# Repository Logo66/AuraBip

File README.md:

# AuraBip — BLE-Vario auf Heltec V4 (Arbeitstitel)

Minimalistisches BLE-Vario im Stodeus-Stil: Heltec WiFi LoRa 32 V4 + GNSS +
BMP581 + LSM6DSO32 + SHT40. OLED zeigt nur das Nötigste, maximal gross.
Zwei Varianten: **silent** (BLE+Display) und **audio** (I2S-Verstärker,
Vario-Ton + Sprachansagen).

© 2026 KIE Engineering. Proprietär. Clean-Room-Regel wie WindBuddy:
kein Code aus GPL/CC-BY-NC-Projekten (GXAirCom, SoftRF, etc.).
Erlaubt: RadioLib/NimBLE/U8g2 als Bibliotheken (MIT/BSD), öffentliche
Protokoll-Spezifikationen (LK8EX1, NMEA).

## Kernidee "Instant Vario"

Reines Baro-Vario ist träge und böenempfindlich. Die Franzosen (Stodeus)
koppeln deshalb Beschleunigungssensor + Barometer. Wir machen dasselbe:
Kalman-Filter mit BMP581 (Messung, ~50 Hz) + LSM6DSO32 Vertikal-
beschleunigung (Prädiktion, ~200 Hz). Ergebnis: Ansprechzeit <100 ms statt
~1 s, ohne Zappeln.

## BLE-Protokoll (Kompatibilität zu XCTrack / XCSoar / SkyDrop-Apps)

Nordic UART Service (NUS), Notify-Stream mit:
- `$LK8EX1,<press_Pa>,<alt_m>,<vario_cm_s>,<temp_C>,<batt>*CS` — 5 Hz
- NMEA `$GPGGA` / `$GPRMC` Passthrough vom GNSS — 1 Hz
⚠️ VERIFY: LK8EX1-Feldreihenfolge/Checksumme gegen offizielle Doku (T1).

## Display-Philosophie

128×64 OLED, eine einzige Ansicht im Flug:
```
+----------------------+
|  +2.4          ← Vario, riesig (32 px Ziffern)
|  1847 m   34 km/h    ← Alt + GPS-Speed, klein
+----------------------+
```
Kein Menü im Flug. Konfiguration über BLE (BipLink-Prinzip) — Ticket T5.

## Audio-Variante — Realitätscheck

"High Quality Sprach- und Varioton" geht NICHT über den nackten Piezo.
Stodeus-Qualität heisst: richtiger Lautsprecher + Verstärker.
Unser Weg: **MAX98357A I2S-Amp (~3 CHF) + 1 W / 8 Ω Lautsprecher 20–28 mm**.
- Varioton: Synthese direkt auf dem S3 (Sinus/Rechteck, Tonhöhe+Rate aus Vz)
- Sprache: WAV-Samples (16 kHz mono) im 16-MB-Flash — Ansagen Höhe/Speed/
  Steigen auf Doppeltipp (IMU-Tap-Detection des LSM6DSO32, kein Taster nötig!)
Samples: selbst mit TTS generieren (de/en/es — es für Kolumbien 😉).

## Hardware-Verkabelung (v0.1 Prototyp)

| Signal | Heltec V4 Pin | Anmerkung |
|---|---|---|
| I2C SDA/SCL | 17 / 18 (⚠️ VERIFY am V4-Schema) | BMP581 0x47, LSM6DSO32 0x6A, SHT40 0x44 — Ivos Standard-Map |
| GNSS | SH1.25-8P Connector | ⚠️ VERIFY Pinout/UART lt. V4-Doku (T2) |
| OLED | onboard | SSD1306 128×64 |
| I2S (audio) | BCLK/LRCK/DIN frei wählen | in config.h |

## Strategie-Notiz

Hardware-Kosten ~35–45 CHF (Board+Sensoren+GNSS). Als Bausatz das perfekte
Einstiegsprodukt unterhalb der Aura Krücke — und der SX1262 ist ja onboard:
FANET-Upgrade per Firmware-Update ist der eingebaute Upsell (v2).

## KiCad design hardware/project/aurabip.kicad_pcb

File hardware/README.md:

# AuraBip audio — Hardware v0.1 (Serienprodukt)

© 2026 KIE Engineering. Proprietär.

Kompaktes BLE-Vario mit Ton-/Sprachausgabe **und FANET-TX** (FANET→OGN;
ADS-L-ready für den kommenden Conspicuity-Standard): **36×52 mm, 4 Lagen, doppelseitig bestückt**.
Vorderseite: MCU, Sensorik, GNSS, Audio, Power. Rückseite: E22-900M22S
(SX1262) + u.FL-Antennenbuchse. OLED-Modul gesteckt über der Vorderseite,
Akku (LiPo 802030) und Lautsprecher extern per JST-PH.

## Struktur

```
hardware/
  BOM.md          Stückliste + bewusste Design-Entscheide + VERIFY-Tickets
  PINMAP.md       GPIO-Zuordnung, Power-Topologie, komplette Netzliste
  lib/            aurabip.kicad_sym + aurabip.pretty (eigene Symbole/Footprints)
  project/        aurabip.kicad_sch / aurabip.kicad_pcb (generiert!)
  scripts/        generate_schematic.py / generate_pcb.py / symlib.py
  route/          FreeRouting-Pipeline (fanout -> DSN -> route -> import -> DRC)
```

**Alles generiert:** Schema und PCB entstehen aus den Python-Skripten —
Änderungen bitte dort machen und neu generieren, nicht im GUI editieren
(sonst divergiert die Quelle der Wahrheit). Workflow:

```powershell
# 1. Schema (schreibt auch lib/aurabip.kicad_sym + Lib-Tables)
& "C:\Program Files\KiCad\10.0\bin\python.exe" scripts\generate_schematic.py
# 2. ERC
& "C:\Program Files\KiCad\10.0\bin\kicad-cli.exe" sch erc project\aurabip.kicad_sch
# 3. PCB (Platzierung + Zonen, ohne Tracks; zieht Netzliste aus dem Schema)
& "C:\Program Files\KiCad\10.0\bin\python.exe" scripts\generate_pcb.py
# 4. Routing + DRC
powershell -File route\run_autoroute.ps1   # -> project\aurabip_routed.kicad_pcb
```

## Floorplan (Blick von oben)

```
+--------------------------------+
|      L96 GNSS (Patch oben)     |  <- Antenne Richtung Himmel
|                        [AKKU]  |
| ESP32-S3    BMP581  SHT40      |
| (Antenne    LSM6DSO32   [OLED- |
|  -> links)  Pullups      Hdr]  |
| LDO  Teiler  MAX98357A         |
| SW1  USBLC6  Lader  [SPEAKER]  |
| [RST] USB-C [BOOT]  Testpads   |
+--------------------------------+
```

- **ESP32-Antenne**: linke Kante, Kupfer-Keepout auf allen Lagen (x 0–6.0, y 17.7–34.3)
- **L96-Patch**: obere Kante, GND-Lage bleibt darunter (Quectel-Empfehlung, VERIFY T-H5)
- **BMP581/SHT40**: nahe Boardkante; fürs Gehäuse Druckausgleichs-/Lüftungsöffnung vorsehen
- **Rückseite**: E22-900M22S mittig (Handbestückung), u.FL darunter — 868-Flexantenne
  im Gehäuse verlegen, weg von GNSS-Patch und BLE-Antenne (T-H8)
- Lagen: F=Signal+GND-Pour, In1=GND, In2=+3V3, B=Signal+GND-Pour

## Fertigung

- JLCPCB 4-Lagen, 1.6 mm, min. Track/Clearance 0.10 mm (Via 0.5/0.3),
  Bohrloch→Kupfer 0.2 mm — Standardprozess (T-H1 verifizieren)
- SMT-Bestückung (Vorderseite): alle Passiven 0402/0603 aus JLC-Basic-Sortiment
- Handbestückung: L96, JST-Stecker, OLED-Header, Rückseite (E22, u.FL, C14/C15)

## Firmware-Anpassung

Serien-Board ≠ Heltec-Prototyp — `src/config.h` braucht die Pin-Werte aus
[PINMAP.md](PINMAP.md) (I2C 8/9, GNSS 17/18, I2S 4/5/6, neu: AMP_SD 7,
VBAT_ADC 1, LED 2, BTN 0, LoRa-SPI 21/12/11/13 + BUSY 14/DIO1 3/RST 15/
TXEN 16/RXEN 37; OLED auf dem Sensorbus, kein Vext).

**FANET-TX**: Encoder aus WindBuddy `lib/fanet` übernehmen (eigener
Clean-Room-Code, Tracking Typ 1 statt Wetter Typ 4). RadioLib mit
`setRfSwitchPins(RXEN, TXEN)`. TX-Leistung hart ≤ 14 dBm ERP (T-H8),
nur im Flug senden, Adresse/Manufacturer wie WindBuddy-Konvention.

## Offene VERIFY-Tickets (vor Bestellung!)

| Ticket | Was |
|---|---|
| T-H1 | LCSC-Nummern + Lagerbestand aller Positionen |
| T-H2 | **L96-Padout** gegen Quectel Hardware Design Guide (Footprint ist Annahme!) |
| T-H3 | MAX98357A: TQFN-Pinnummern + Exposed-Pad-Maß gegen Maxim-Datenblatt |
| T-H4 | LSM6DSO32-Pinout (INT1=Pin 4?) gegen ST-Datenblatt |
| T-H5 | Antennen-Regeln: ESP32-Keepout-Maße + GND unter L96-Patch |
| T-H6 | USB-C-Footprint-Orientierung: Stecker muss über die Boardkante ragen |

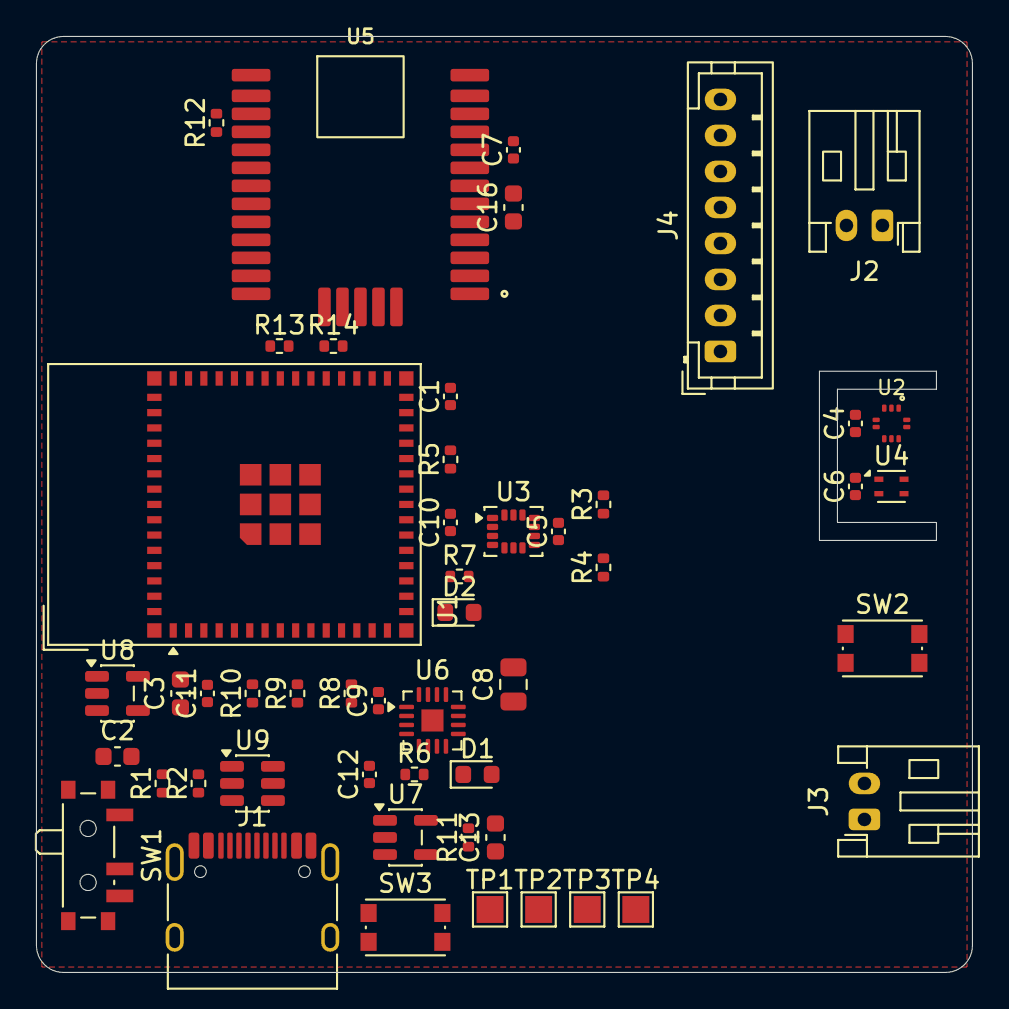
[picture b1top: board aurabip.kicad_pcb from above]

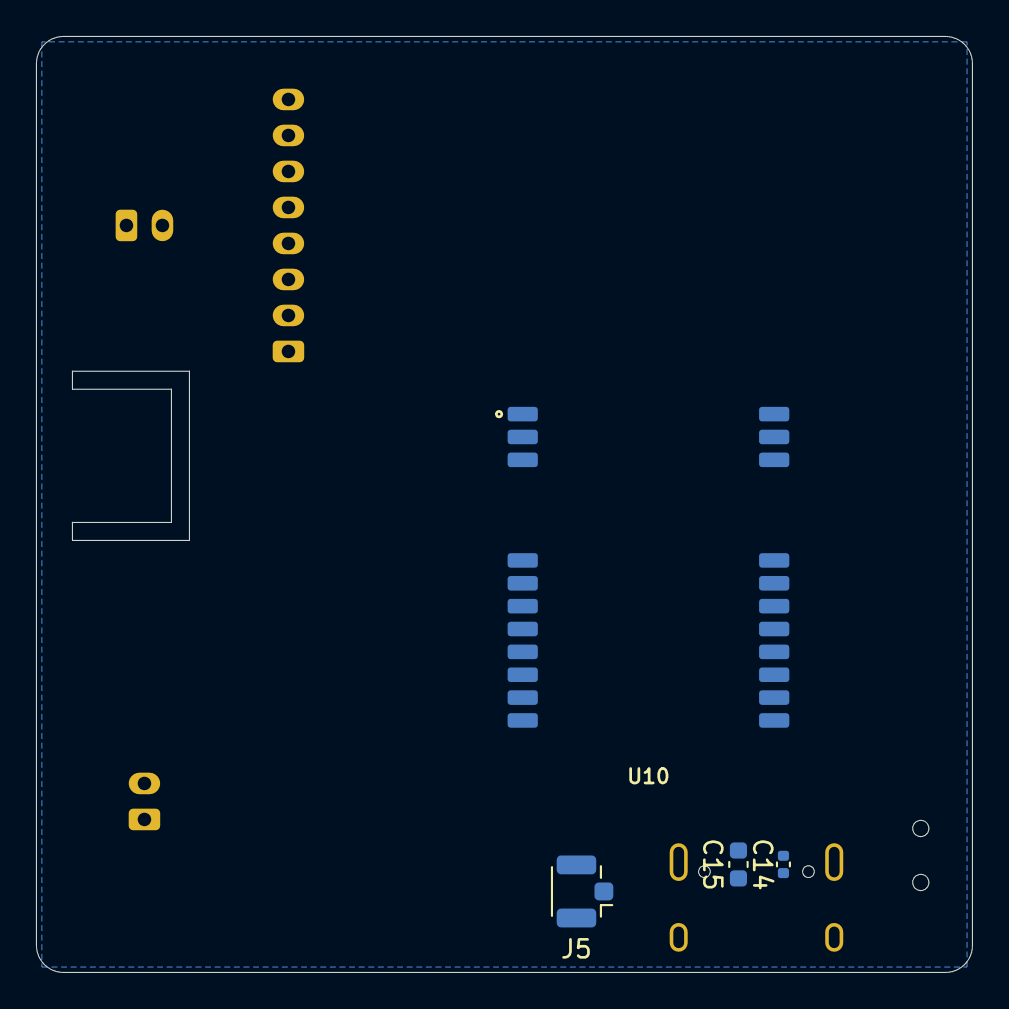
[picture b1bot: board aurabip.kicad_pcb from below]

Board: 4 copper layers, 52.0 x 52.0 mm, 54 parts (4 on the bottom side), 48 nets, no tracks yet.

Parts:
C1, C4, C5, C6, C7, C9, C11, C12, C14: 100n; C_0402_1005Metric
C2, C3, C15, C16: 10u; C_0603_1608Metric
C8: 22u; C_0805_2012Metric
C10: 1u; C_0402_1005Metric
C13: 4.7u; C_0603_1608Metric
D1: CHG; LED_0603_1608Metric
D2: STATUS; LED_0603_1608Metric
J1: USB-C; USB_C_Receptacle_HRO_TYPE-C-31-M-12
J2: AKKU; JST_PH_S2B-PH-K_1x02_P2.00mm_Horizontal
J3: SPEAKER; JST_PH_S2B-PH-K_1x02_P2.00mm_Horizontal
J4: OLED SPI; JST_PH_B8B-PH-K_1x08_P2.00mm_Vertical
J5: u.FL 868; U.FL_Hirose_U.FL-R-SMT-1_Vertical
R1, R2: 5.1k; R_0402_1005Metric
R3, R4: 4.7k; R_0402_1005Metric
R5: 10k; R_0402_1005Metric
R6, R7, R13: 1k; R_0402_1005Metric
R8: 100k; R_0402_1005Metric
R9, R10: 1M; R_0402_1005Metric
R11, R14: 2k; R_0402_1005Metric
R12: 0R; R_0402_1005Metric
SW1: EIN/AUS; SW_SPDT_PCM12
SW2: RESET; SW_Push_1P1T_NO_CK_KMR2
SW3: BOOT; SW_Push_1P1T_NO_CK_KMR2
TP1: IO33; TestPoint_Pad_1.5x1.5mm
TP2: IO34; TestPoint_Pad_1.5x1.5mm
TP3: IO35; TestPoint_Pad_1.5x1.5mm
TP4: IO36; TestPoint_Pad_1.5x1.5mm
U1: ESP32-S3-MINI-1; ESP32-S3-MINI-1_compact
U2: BMP581; BMP581_LGA-10_2x2mm
U3: LSM6DSO32; LGA-14_3x2.5mm_P0.5mm_LayoutBorder3x4y
U4: SHT40; Sensirion_DFN-4_1.5x1.5mm_P0.8mm_SHT4x_NoCentralPad
U5: L96; Quectel_L96
U6: MAX98357A; TQFN-16-1EP_3x3mm_P0.5mm_EP1.23x1.23mm
U7: MCP73831; SOT-23-5
U8: AP2112K-3.3; SOT-23-5
U9: USBLC6; SOT-23-6
U10: E22-900M22S; E22_900M22S

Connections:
+3V3: C1.1, C3.1, C4.1, C5.1, C6.1, C7.1, C14.1, C15.1, C16.1, J4.1, R3.1, R4.1, R5.1, R8.1, U1.3, U2.1, U2.5, U2.6, U2.10, U3.5, U3.8, U3.12, U4.3, U5.8, U5.9, U8.5, U10.9
AMP_SD: R8.2, U1.11, U6.4
BTN_BOOT: SW3.1, U1.4
CC1: J1.A5, R1.1
CC2: J1.B5, R2.1
CHG_LED_A: D1.2, R6.2
CHG_STAT: D1.1, U7.1
ESP_EN: C10.1, R5.2, SW2.1, U1.45
GND: C1.2, C2.2, C3.2, C4.2, C5.2, C6.2, C7.2, C8.2, C9.2, C10.2, C11.2, C12.2, C13.2, C14.2, C15.2, C16.2, D2.1, J1.A1, J1.A12, J1.B1, J1.B12, J1.SH, J2.2, J4.2, J5.2, R1.2, R2.2, R10.2, R11.2, R14.2, SW1.3, SW2.2, SW3.2, U1.1, U1.2, U1.42, U1.43, U1.46, U1.47, U1.48, U1.49, U1.50, U1.51, U1.52, U1.53, U1.54, U1.55, U1.56, U1.57, U1.58, U1.59, U1.60, U1.61, U1.62, U1.63, U1.64, U1.65, U2.3, U2.8, U2.9, U3.1, U3.6, U3.7, U4.4, U5.4, U5.5, U5.10, U5.11, U5.12, U5.13, U5.14, U5.15, U5.18, U5.19, U5.21, U5.22, U5.27, U5.31, U6.3, U6.11, U6.15, U6.17, U7.2, U8.2, U9.2, U10.1, U10.2, U10.3, U10.4, U10.5, U10.10, U10.11, U10.12, U10.20, U10.22
GNSS_RXD: R13.1, U1.22
GNSS_RXD_DIV: R13.2, R14.1, U5.26
GNSS_TXD: U1.21, U5.25
I2C_SCL: R4.2, U1.13, U2.2, U3.13, U4.2
I2C_SDA: R3.2, U1.12, U2.4, U3.14, U4.1
I2S_BCLK: U1.8, U6.16
I2S_DOUT: U1.10, U6.1
I2S_LRCK: U1.9, U6.14
IMU_INT1: U1.14, U3.4
L96_RFIN: R12.2, U5.17
L96_RFOUT: R12.1, U5.16
LDO_EN: SW1.2, U8.3
LED2_A: D2.2, R7.2
LED_STATUS: R7.1, U1.6
LORA_ANT: J5.1, U10.21
LORA_BUSY: U1.18, U10.14
LORA_DIO1: U1.7, U10.13
LORA_NSS: U1.25, U10.19
LORA_RST: U1.19, U10.15
LORA_RXEN: U1.33, U10.6
LORA_TXEN: U1.20, U10.7
OLED_CS: J4.5, U1.28
OLED_DC: J4.6, U1.29
OLED_RST: J4.7, U1.31
PROG: R11.1, U7.5
SPI2_MISO: U1.17, U10.16
SPI2_MOSI: J4.3, U1.15, U10.17
SPI2_SCK: J4.4, U1.16, U10.18
SPK_N: J3.2, U6.10
SPK_P: J3.1, U6.9
TP_IO38: TP1.1, U1.34
TP_IO40: TP2.1, U1.36
TP_IO41: TP3.1, U1.37
TP_IO42: TP4.1, U1.38
USB_DN: J1.A7, J1.B7, U1.23, U9.1, U9.6
USB_DP: J1.A6, J1.B6, U1.24, U9.3, U9.4
VBAT: C2.1, C8.1, C9.1, C13.1, J2.1, R9.1, SW1.1, U6.7, U6.8, U7.3, U8.1
VBAT_SENSE: C11.1, R9.2, R10.1, U1.5
VBUS: C12.1, J1.A4, J1.A9, J1.B4, J1.B9, R6.1, U7.4, U9.5

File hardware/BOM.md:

# AuraBip audio — BOM v0.1 (Serienprodukt)

© 2026 KIE Engineering. Proprietär.

Ziel: kompaktes BLE-Vario mit Sprach-/Tonausgabe, ~35×48 mm, 4-Lagen-PCB,
JLCPCB-Fertigung (SMT-Bestückung ab Rolle wo möglich).
Alle LCSC-Nummern sind ⚠️ **vor Bestellung zu verifizieren** (Verfügbarkeit dreht schnell).

## Kern

| Ref | Bauteil | Package | Funktion | LCSC (⚠️ prüfen) | ~Preis (1 Stk) |
|---|---|---|---|---|---|
| U1 | **ESP32-S3-MINI-1-N8** | Modul 15.4×15.4 | MCU, BLE 5, natives USB (kein UART-Bridge-Chip nötig), FCC/CE-zertifiziert | C2913204 | 3.20 CHF |
| U2 | **BMP581** | LGA-10 2×2 | Barometer 50 Hz (Kalman-Update), Adr 0x47 | TBD | 2.50 CHF |
| U3 | **LSM6DSO32XTR** | LGA-14 2.5×3 | IMU ±32 g, 200 Hz Prädiktion + Tap-Detection, Adr 0x6A | TBD | 2.80 CHF |
| U4 | **SHT40-AD1B** | DFN-4 1.5×1.5 | Temp/Feuchte, Adr 0x44 | TBD | 1.80 CHF |
| U5 | **Quectel L96-M33** | LCC 14×15 | GNSS MT3333, **integrierte Patch-Antenne** (kein RF-Design-Risiko), 1 Hz NMEA | TBD | 6.50 CHF |
| U6 | **MAX98357AETE+T** | TQFN-16-EP 3×3 | I2S-DAC+3.2W-Class-D-Amp, läuft direkt an VBAT | TBD | 2.20 CHF |

## Power

| Ref | Bauteil | Package | Funktion | LCSC (⚠️ prüfen) | ~Preis |
|---|---|---|---|---|---|
| U10 | **Ebyte E22-900M22S** | Modul 16×26 | SX1262 + TCXO + PA, FANET-TX (Typ 1) → OGN-Sichtbarkeit (Pflicht ab 2027). TX-Leistung in FW hart auf 14 dBm ERP begrenzt | TBD | 5.50 CHF |
| J5 | **u.FL / IPEX** Buchse (Hirose U.FL-R-SMT-1) | SMD | 868-MHz-Antennenanschluss | TBD | 0.40 CHF |
| ANT | **Molex 105262-0001** Flex-Klebeantenne 868/915, u.FL, 100 mm Kabel (Alt.: Taoglas FXP14; -0002 = 150 mm Kabel) | im Gehäuse (Wandnische, vertikal) | Nischenmaß im Fusion-Skript an Element anpassen (ant_l/ant_h) | Beta LAYOUT ~8 € | 8.00 CHF |
| U7 | **MCP73831T-2ACI/OT** | SOT-23-5 | LiPo-Lader 1 Zelle, 500 mA (R_PROG 2 kΩ) | C424093 | 0.60 CHF |
| U8 | **ME6217C33M5G** | SOT-23-5 | LDO 3.3 V / **800 mA** (ESP32-BLE-Peak + LoRa-TX + GNSS gleichzeitig; Amp hängt an VBAT). Pinkompatibel zu AP2112K | C82942 (⚠️) | 0.20 CHF |
| U9 | **USBLC6-2SC6** | SOT-23-6 | USB-ESD-Schutz | C7519 | 0.20 CHF |
| J1 | **TYPE-C-31-M-12** (HRO) | USB-C 16P | Laden + Flashen (USB-CDC/DFU) | C165948 | 0.25 CHF |
| J2 | **JST PH 2P** (S2B-PH-K-S) | THT gewinkelt | Akku-Anschluss | TBD | 0.10 CHF |
| BAT | **LiPo 504050**, 3.7 V, **1500 mAh**, 52×42×5 mm, 25 g, −25…+60 °C, Kabel 45 mm, JST-PH 2.0 | extern, unter dem 52×52-Board (Gehäuse-Schacht) | ~10 h Laufzeit bei ~140 mA Mix; Betriebstemp. bis −25 °C ist flugtauglich. ⚠️ **POLARITÄT am Stecker prüfen** — bei LiPo-Herstellern nicht genormt! | ~9 CHF | 9.00 CHF |
| SW1 | **MSK-12C02** | Schiebeschalter | Ein/Aus (schaltet nur LDO-EN, nicht VBAT — Laden geht auch „aus") | TBD | 0.15 CHF |

## Audio & UI

| Ref | Bauteil | Package | Funktion | LCSC (⚠️ prüfen) | ~Preis |
|---|---|---|---|---|---|
| LS1/J3 | **Visaton K 28 WP** (28 mm, 8 Ω, 1 W, spritzwassergeschützte Kunststoffmembran) an JST-PH-Pigtail | — | Varioton + Sprache; WP-Variante wegen Outdoor-Einsatz | Voelkner/RS/Reichelt ~4 CHF | 4.00 CHF |
| J4 | **JST-PH 8-Pin vertikal** (B8B-PH-K-S) + **Waveshare 1.32" OLED** 128×96, 16 Graustufen, SSD1327, SPI | Kabel (liegt Modul bei) | Kein Header — Modul hat **PH2.0-Buchse**, Kabel im Lieferumfang → Display frei im Gehäusedeckel platzierbar. Teilt SPI2 mit E22 (eigener CS); −20…70 °C. T-H9: Kabel-Pinreihenfolge bei Lieferung prüfen | Waveshare/Amazon ~12 CHF | 12.00 CHF |
| SW2 | Taster **RESET** (EN) | SMD 3.9×2.9 | Neustart | TBD | 0.05 CHF |
| SW3 | Taster **BOOT/USER** (GPIO0) | SMD 3.9×2.9 | Strapping + Nutzertaste im Betrieb (Doppeltipp macht die IMU) | TBD | 0.05 CHF |
| D1 | LED grün + R 1 kΩ | 0603 | Lade-Status (MCP73831 STAT) | — | 0.03 CHF |
| D2 | LED blau + R 1 kΩ | 0603 | Status (GPIO2) | — | 0.03 CHF |

## Passiv (0402, JLC Basic Parts)

| Menge | Wert | Funktion |
|---|---|---|
| 2× | 5.1 kΩ | USB-C CC1/CC2 |
| 2× | 4.7 kΩ | I2C-Pullups SDA/SCL |
| 1× | 2 kΩ | MCP73831 PROG (500 mA) |
| 2× | 1 MΩ | VBAT-ADC-Teiler (GPIO1) |
| 1× | 100 kΩ | Amp SD_MODE-Pullup auf 3V3 (aus, wenn 3V3 aus) |
| 1× | 10 kΩ | EN-Pullup (RESET) |
| 8× | 100 nF | Abblock je IC |
| 2× | 10 µF | LDO in/out |
| 1× | 22 µF (0805) | Amp-VBAT-Puffer |
| 1× | 100 nF | ADC-Teiler-Filter |

**Summe Elektronik: ~31 CHF/Stk** (Kleinserie 50 Stk, ohne PCB/Bestückung/Akku/Gehäuse).
PCB+SMT bei JLC (50 Stk, 4-Lagen): ~9 CHF/Board. Akku 802030: ~3 CHF. Antenne 868: ~1 CHF. → **~44 CHF Material.**

## Bewusste Entscheidungen

- **FANET-TX drin** (Änderung 2026-07-03): Elektronische Sichtbarkeits-Pflicht (FLARM/FANET/OGN) ab 2027 → SX1262-Modul E22-900M22S. **Nur TX** (Tracking Typ 1, FANET→OGN), keine Warnlogik — Warnquellen-Philosophie bleibt. FANET-Encoder aus WindBuddy `lib/fanet` (eigener Clean-Room-Code) wiederverwenden. Modul statt nacktem SX1262: TCXO (Frequenzstabilität bei Kälte!) + fertiges RF-Frontend.
- **Kein USB-UART-Chip**: ESP32-S3 natives USB (GPIO19/20) für Flashen + CDC-Logs.
- **Kein Fuel-Gauge** (v1): VBAT-Teiler an ADC reicht für %-Anzeige. v2-Option: MAX17048.
- **Kein Power-Path** (v1): MCP73831 lädt, System zieht parallel an VBAT. Bekannte Schwäche: Terminierung bei Last ungenau. v2-Option: BQ24074.
- **L96 mit integrierter Antenne** statt ATGM336H+Antenne: teurer, aber null RF-Layout-Risiko und kleiner als Patch+Pigtail.
- **Amp an VBAT**: Audio-Peaks (~1 A kurz) gehen nicht durch den 600-mA-LDO. SD_MODE-Pullup an 3V3 schaltet den Amp mit aus.

## VERIFY-Status (Stand 2026-07-05)

| Ticket | Status |
|---|---|
| T-H2 L96-Padout | ✅ **verifiziert** gegen Quectel HW Design V1.4 (LCC-31, 14×9.6! RF-Brücke R12 + RXD-Teiler R13/R14 ergänzt, Antennen-Keepout 4.8×7.3) |
| T-H3 MAX98357A | ✅ **verifiziert** gegen ADI-Datenblatt Rev 7 (TQFN-Pinout war falsch → korrigiert; Footprint auf EP1.23 gewechselt; GAIN offen = 9 dB bestätigt) |
| T-H4 LSM6DSO32 | ✅ **verifiziert** gegen ST-Datenblatt Rev 1 (Pinout korrekt; Footprint auf ST-LayoutBorder3x4y gewechselt) |
| T-H7 E22-900M22S | ✅ **verifiziert** gegen Ebyte Manual v1.3 (war 14×20/1.27er-Pitch statt 16×26/2.2 — komplett neu; JLC C411293) |
| T-H1 LCSC/PCBWay-Nummern + Lager | ⏳ offen — bei Bestellung gegen PCBWay-Sortiment prüfen |
| T-H5 ESP32-Antennen-Keepout-Maße | ⏳ offen (konservativ ausgelegt) |
| T-H6 USB-C-Überstand | ⏳ offen — 1.2 mm Nase, am ersten Board messen |
| T-H8 Regulatorik 14 dBm ERP + Duty Cycle | ⏳ offen (vor Verkauf, mit Antennengewinn rechnen) |
| T-H9 OLED-Kabel-Aderreihenfolge | ⏳ offen — bei Lieferung Sichtprüfung |

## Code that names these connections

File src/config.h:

// AuraBip — Konfiguration
// © 2026 KIE Engineering. Proprietär.
#pragma once

#define DEVICE_NAME       "AuraBip"

// I2C-Adressen (beide Boards gleich)
#define I2C_ADDR_BMP581   0x47
#define I2C_ADDR_LSM6     0x6A
#define I2C_ADDR_SHT40    0x44

#ifdef BOARD_SERIES
// ============================================================================
// Serienboard v0.1 — ESP32-S3-MINI-1 (Referenz: hardware/PINMAP.md)
// ============================================================================

// --- I2C (ein Bus: BMP581 + LSM6DSO32 + SHT40) ---
#define PIN_I2C_SDA       8
#define PIN_I2C_SCL       9
#define PIN_IMU_INT       10   // LSM6DSO32 INT1 (Tap/Data-Ready, v0.1 ungenutzt)

// --- Audio: I2S -> MAX98357A ---
#define PIN_I2S_BCLK      4
#define PIN_I2S_LRCK      5
#define PIN_I2S_DOUT      47   // Routing-Umzug 2026-07-06: IO6 -> IO47 (s. PINMAP.md)
#define PIN_AMP_SD        7    // high = Amp an (100k-Pullup an 3V3)

// --- GNSS: Quectel L96 an UART1 ---
#define PIN_GNSS_RX       17   // <- L96 TXD
#define PIN_GNSS_TX       18   // -> L96 RXD
#define GNSS_BAUD         9600

// --- LoRa: E22-900M22S (SX1262) an SPI2, geteilt mit OLED ---
#define PIN_SPI_SCK       12
#define PIN_SPI_MOSI      11
#define PIN_SPI_MISO      13
#define PIN_LORA_NSS      21
#define PIN_LORA_DIO1     3
#define PIN_LORA_BUSY     14
#define PIN_LORA_RST      15
#define PIN_LORA_TXEN     16
#define PIN_LORA_RXEN     37

// --- OLED SSD1327 (Variante vision, geteilter SPI2-Bus) ---
#define PIN_OLED_CS       33
#define PIN_OLED_DC       34
#define PIN_OLED_RST      35

// --- Sonstiges ---
#define PIN_VBAT_ADC      1    // Teiler 1M/1M -> VBAT/2
#define PIN_LED           2    // Status-LED, aktiv high
#define PIN_BTN           0    // BOOT/USER-Taster (aktiv low)

#else
// ============================================================================
// Heltec V3/V4 Prototyp — Sensorik simuliert (sensors_stub.cpp)
// ============================================================================

// --- I2C (⚠️ VERIFY Pins am V4-Schema; V3: SDA=17 SCL=18 fürs OLED-Bus) ---
#define PIN_I2C_SDA       41   // externer Sensorbus (getrennt vom OLED-Bus möglich)
#define PIN_I2C_SCL       42

// --- OLED (onboard, eigener Bus beim Heltec) ---
#define PIN_OLED_SDA      17
#define PIN_OLED_SCL      18
#define PIN_OLED_RST      21
#define PIN_VEXT          36   // OLED/Peripherie-Versorgung (LOW = an) ⚠️ VERIFY V4

// --- GNSS (SH1.25-8P) ⚠️ VERIFY Pinout aus V4-Doku (T2) ---
#define PIN_GNSS_RX       33
#define PIN_GNSS_TX       34
#define GNSS_BAUD         9600

// --- Audio-Variante (nur bei -D VARIANT_AUDIO) ---
#define PIN_I2S_BCLK      6
#define PIN_I2S_LRCK      5
#define PIN_I2S_DOUT      7

#endif // BOARD_SERIES

#define AUDIO_SAMPLE_RATE 16000

// --- Vario-Filter ---
#define BARO_RATE_HZ      50
#define IMU_RATE_HZ       200
#define KF_ACCEL_NOISE    0.3f    // m/s² Prozessrauschen (tunen im Flug)
#define KF_BARO_NOISE     0.35f   // m Messrauschen BMP581 (tunen)

// --- Ton-Engine (audio) ---
#define TONE_CLIMB_ON_MS_BASE   350
#define TONE_BASE_FREQ_HZ       600
#define TONE_FREQ_PER_MS        120   // Hz pro m/s Steigen
#define SINK_ALARM_MS           -3.5f // Dauerton unterhalb

// --- BLE ---
#define LK8EX1_RATE_HZ    5

// --- FANET (nur Serienboard, nur TX) ---
#define FANET_TX_ENABLED        1
#define FANET_TX_INTERVAL_MS    5000
#define FANET_TX_DBM            14
#define FANET_TCXO_VOLT         1.8f  // E22-900M22S: TCXO an DIO3, 1.8 V
#define FANET_FREQ_MHZ          868.2f
#define FANET_AIRCRAFT_TYPE     1     // 1 = Paraglider
// Flugerkennung: GPS-Fix + Speed-Schwelle mit Hysterese
#define FLIGHT_START_KMH        10.0f
#define FLIGHT_STOP_KMH         5.0f
#define FLIGHT_STOP_HOLD_MS     60000
